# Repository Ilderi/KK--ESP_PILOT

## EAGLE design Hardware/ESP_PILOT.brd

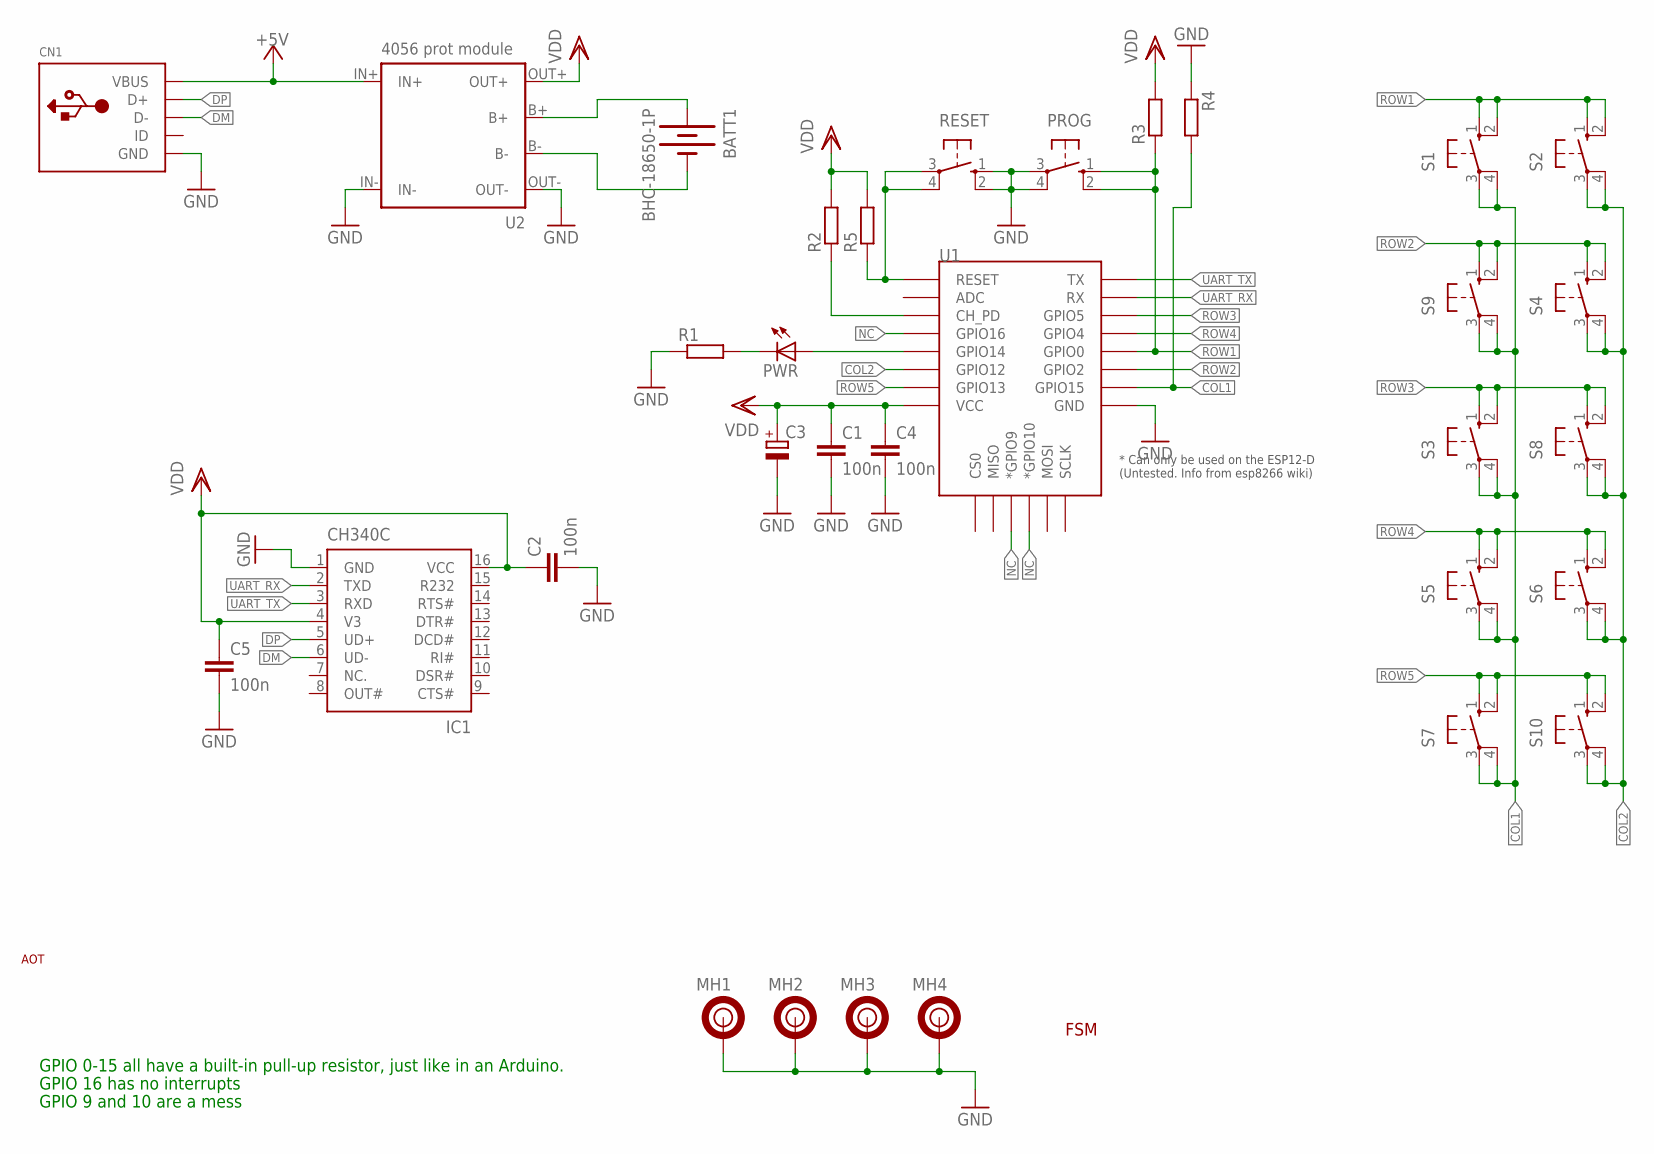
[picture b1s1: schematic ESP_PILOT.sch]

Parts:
BATT1: BHC-18650-1P
C1, C2, C4, C5: 100n; C050-025X075
C3: CPOL-EUE2.5-7; E2,5-7
CN1: USBMINIB; USB-MINIB
IC1: CH340C; SOIC16N
MH1, MH2, MH3, MH4: MOUNTING_HOLE_3MM; 3MM_CONDUCTING
PROG: 10-XX; B3F-10XX
PWR: LED5MM
R1, R2, R3, R4, R5: R-EU_0207/10; 0207/10
RESET: 10-XX; B3F-10XX
S1, S2, S3, S4, S5, S6, S7, S8, S9, S10: 10-XX; B3F-10XX
U1: ESP12ESMD; ESP12E-SMD
U2: 4056 prot module; TP4056_MICRO/MINI_PROT
U$1: FSM
U$2: AOT

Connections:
+5V: CN1.VBUS, U2.IN+
COL1: R4.2, S1.3, S1.4 (P1), S3.3, S3.4 (P1), S5.3, S5.4 (P1), S7.3, S7.4 (P1), S9.3, S9.4 (P1), U1.GPIO15
COL2: S2.3, S2.4 (P1), S4.3, S4.4 (P1), S6.3, S6.4 (P1), S8.3, S8.4 (P1), S10.3, S10.4 (P1), U1.GPIO12
DM: CN1.D-, IC1.6 (UD-)
DP: CN1.D+, IC1.5 (UD+)
GND: C1.2, C2.2, C3.-, C4.2, C5.2, CN1.GND, IC1.1 (GND), MH1.1, MH1.2, MH1.3, MH1.4, MH1.5, MH1.6, MH1.7, MH1.8, MH1.O, MH2.1, MH2.2, MH2.3, MH2.4, MH2.5, MH2.6, MH2.7, MH2.8, MH2.O, MH3.1, MH3.2, MH3.3, MH3.4, MH3.5, MH3.6, MH3.7, MH3.8, MH3.O, MH4.1, MH4.2, MH4.3, MH4.4, MH4.5, MH4.6, MH4.7, MH4.8, MH4.O, PROG.3, PROG.4 (P1), R1.1, R4.1, RESET.1 (S), RESET.2 (S1), U1.GND, U2.IN-, U2.OUT-
unnamed: BATT1.- (+), U2.B+
unnamed: BATT1.+ (-), U2.B-
unnamed: PWR.K (C), R1.2
unnamed: R2.1, U1.CH_PD
unnamed: PWR.A, U1.GPIO14
unnamed: R5.1, RESET.3, RESET.4 (P1), U1.RESET
NC: U1.GPIO9 (*GPIO9), U1.GPIO10 (*GPIO10), U1.GPIO16
ROW1: PROG.1 (S), PROG.2 (S1), R3.1, S1.1 (S), S1.2 (S1), S2.1 (S), S2.2 (S1), U1.GPIO0
ROW2: S4.1 (S), S4.2 (S1), S9.1 (S), S9.2 (S1), U1.GPIO2
ROW3: S3.1 (S), S3.2 (S1), S8.1 (S), S8.2 (S1), U1.GPIO5
ROW4: S5.1 (S), S5.2 (S1), S6.1 (S), S6.2 (S1), U1.GPIO4
ROW5: S7.1 (S), S7.2 (S1), S10.1 (S), S10.2 (S1), U1.GPIO13
UART_RX: IC1.2 (TXD), U1.RXD0 (RX)
UART_TX: IC1.3 (RXD), U1.TXD0 (TX)
VDD: C1.1, C2.1, C3.+, C4.1, C5.1, IC1.4 (V3), IC1.16 (VCC), R2.2, R3.2, R5.2, U1.VCC, U2.OUT+

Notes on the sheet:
GPIO 0-15 all have a built-in pull-up resistor, just like in an Arduino.
GPIO 16 has no interrupts
GPIO 9 and 10 are a mess

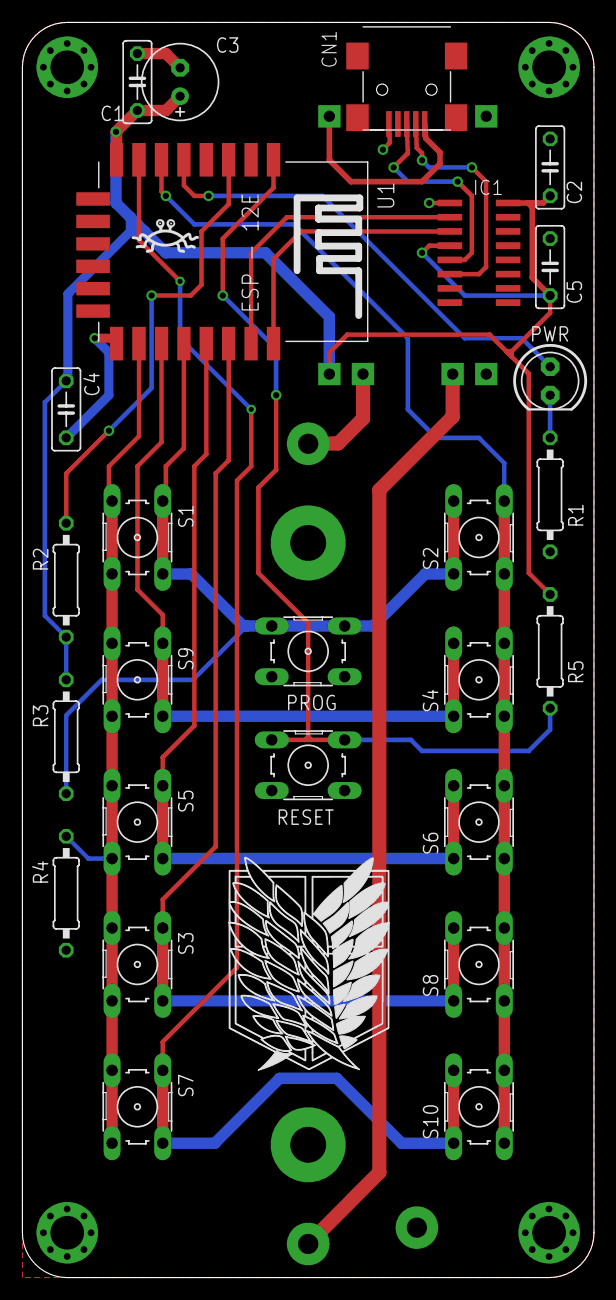
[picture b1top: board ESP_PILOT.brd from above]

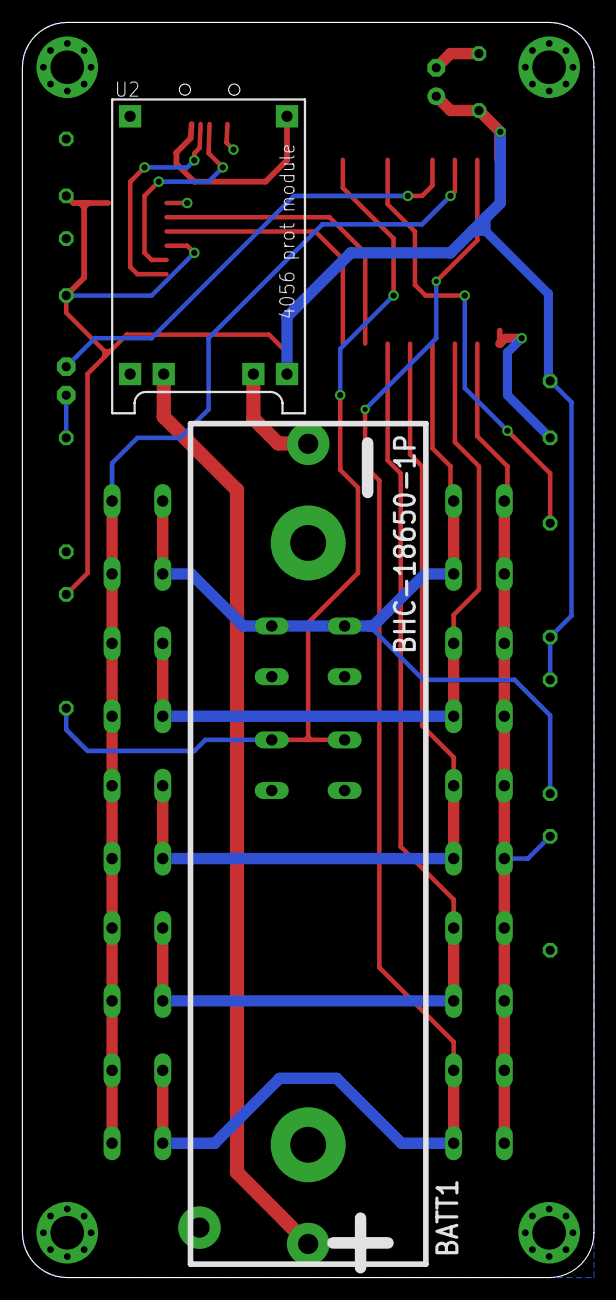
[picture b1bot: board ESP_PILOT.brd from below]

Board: 2 copper layers, 51.0 x 112.0 mm, 34 parts (3 on the bottom side), 21 nets.

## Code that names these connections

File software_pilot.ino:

//settings definitions
#define USB_BAUDRATE 9600

//pins definitons - TODO, dodać piny
#define PIN_ROW1 0 //GPIO0
#define PIN_ROW2 2 //GOIO2
#define PIN_ROW3 5 //GPIO5
#define PIN_ROW4 4 //GPIO4
#define PIN_ROW5 13 //GPIO13
#define PIN_COL1 15 //GPIO15
#define PIN_COL2 12 //GPIO12
#define PIN_LED 14 //GPIO14

//util definitions
#define FOO_OK 1
#define FOO_ERROR 0
#define ROW_COUNT 5
#define COL_COUNT 2
#define BUTTON_COUNT 10
#define DEFAULT_DEBOUNCE_TIME 100

//file scope variables
static const uint8_t row_Pins[] = {PIN_ROW1, PIN_ROW2, PIN_ROW3, PIN_ROW4, PIN_ROW5};
static const uint8_t col_Pins[] = {PIN_COL1, PIN_COL2};
static uint8_t lastPressedButtonID = 0;

typedef struct Button
{
  uint8_t ID;
  uint8_t timeElapsedSincePush;
  uint8_t isDebounced;
}Button;

Button buttons[BUTTON_COUNT] = {0};

//function prototypes
uint32_t findPressedButton();
uint32_t checkButtonsTiming();
uint32_t initializePins();
uint32_t readConfigFromEEPROM();
uint32_t debounceButton();


void setup() {
  initializePins();
  initializeButtons();
}

void loop() {
  findPressedButton();
  //if(Button
  //debounceButton(lastPressedButtonID);
  //if(Button.
}

uint32_t findPressedButton()
{
  
  for(uint8_t i = 0; i < COL_COUNT; i++)
  {
    digitalWrite(col_Pins[i], HIGH);
  }
  
  //loop trhought collumns and rows to find first key pressed, then return it`s ID(number)
  for(uint8_t col = 0; col < COL_COUNT; col++)
  {
    digitalWrite(col_Pins[col], LOW);
    for(uint8_t row = 0; row < ROW_COUNT; row++)
    {
      if(digitalRead(row_Pins[row]) == LOW)
      {
        // col 1 row 3 = button3, col 1 row 3 = button 6 
        uint8_t buttonID = (col+1) * (row+1);
        return (uint32_t)buttonID;
      }
    }
    digitalWrite(col_Pins[col], HIGH);
  }

  return FOO_ERROR;
}

uint32_t initializePins()
{
  //initialize row pins as inputs with pull-up resistors
  for(uint8_t i = 0; i < ROW_COUNT; i++)
  {
    pinMode(row_Pins[i], INPUT_PULLUP);
  }
  //initialize col pins as outputs and set them to LOW state
  for(uint8_t i = 0; i < COL_COUNT; i++)
  {
    pinMode(col_Pins[i], OUTPUT);
    digitalWrite(col_Pins[i], LOW);
  }
  //initialize led pin as output and set it to low state
  pinMode(PIN_LED, OUTPUT);
  digitalWrite(PIN_LED, LOW);

  return FOO_OK;
}

uint32_t initializeButtons()
{
  for(uint8_t i = 0; i < BUTTON_COUNT; i++)
  {
    Button[i].ID = (i+1);
    Button[i].timeElapsedSincePush = 0;
    Button[i].isDebounced = 1;
  }

  return FOO_OK;
}

uint32_t readConfigFromEEPROM()
{
  
}

uint32_t checkButtonsTiming()
{
  
}

uint32_t debounceButton(uint8_t button_ID)
{
  
}

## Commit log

2022-11-28 added proto code
2022-11-29 Algorithm for determining pushed button now works, wake-up on row 4 works
2022-11-30 code refactor + debouncing
2022-12-08 milestone
2022-12-08 Added hardware and renamed software files
2022-12-09 Restored Correct Software Version
2022-12-13 idk if something changed but just in case
2022-12-14 something is not working but core concept is done
2022-12-14 sleep and commands 1-4 work
2022-12-15 fast commit
2023-02-01 Last changes
